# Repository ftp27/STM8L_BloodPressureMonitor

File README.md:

STM8L_BloodPressureMonitor
==========================

Bluetooth remote control for Blood Pressure Monitor on STM8L

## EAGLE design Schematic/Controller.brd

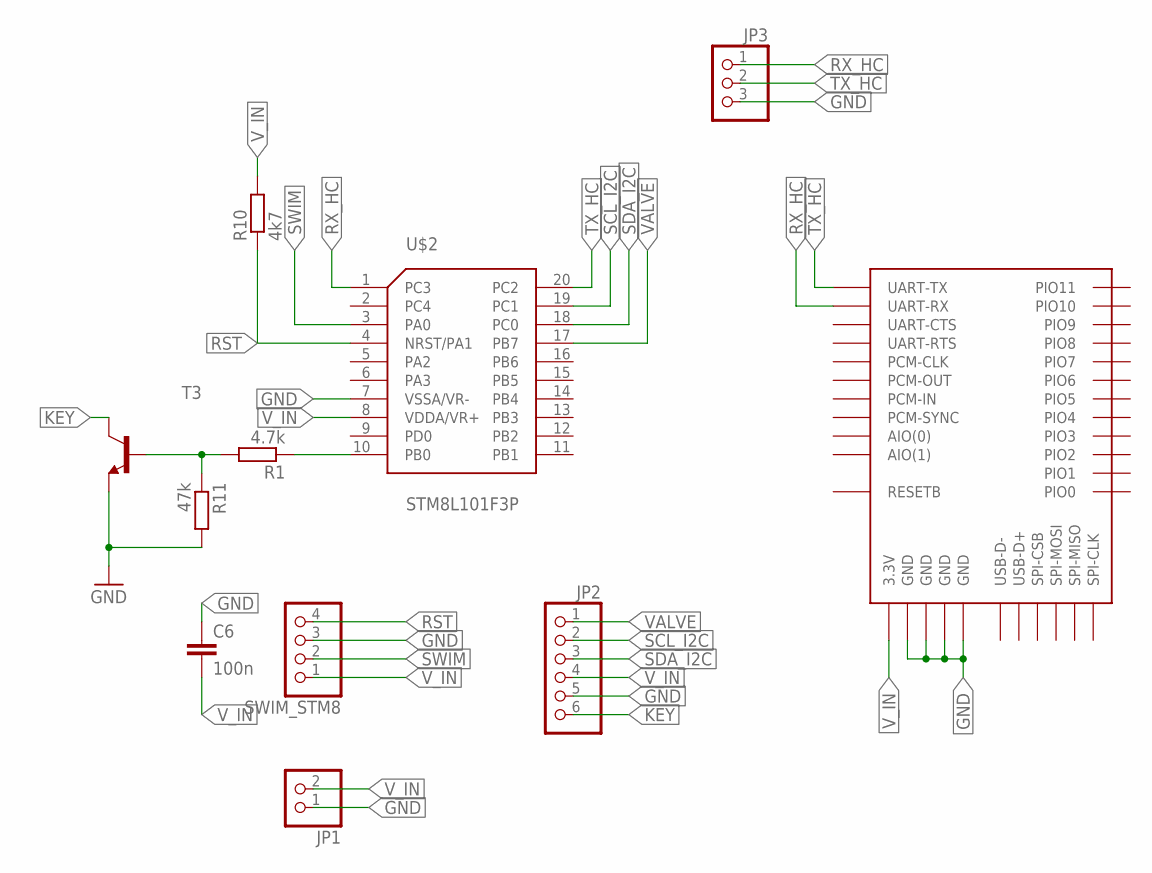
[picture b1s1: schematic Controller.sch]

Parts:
C6: 100n; C0805
JP1: PINHD-1X2; 1X02
JP2: PINHD-1X6; 1X06
JP3: PINHD-1X3; 1X03
R1: 4.7k; R0805
R10: 4k7; R0805
R11: 47k; R0805
SWIM_STM8: PINHD-1X4/90; 1X04/90
T3: BC846B-NPN-SOT23-BEC; SOT23-BEC
U$1: BTM400_6B
U$2: STM8L101F3P

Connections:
GND: C6.1, JP1.1, JP2.5, JP3.3, R11.2, SWIM_STM8.3, T3.E, U$1.GND@1 (GND), U$1.GND@2 (GND), U$1.GND@3 (GND), U$1.GND@4 (GND), U$2.7 (VSSA/VR-)
KEY: JP2.6, T3.C
unnamed: R1.1, U$2.10 (PB0)
unnamed: R1.2, R11.1, T3.B
RST: R10.1, SWIM_STM8.4, U$2.4 (NRST/PA1)
RX_HC: JP3.1, U$1.UART-RX, U$2.1 (PC3)
SCL_I2C: JP2.2, U$2.19 (PC1)
SDA_I2C: JP2.3, U$2.18 (PC0)
SWIM: SWIM_STM8.2, U$2.3 (PA0)
TX_HC: JP3.2, U$1.UART-TX, U$2.20 (PC2)
VALVE: JP2.1, U$2.17 (PB7)
V_IN: C6.2, JP1.2, JP2.4, R10.2, SWIM_STM8.1, U$1.3.3V, U$2.8 (VDDA/VR+)

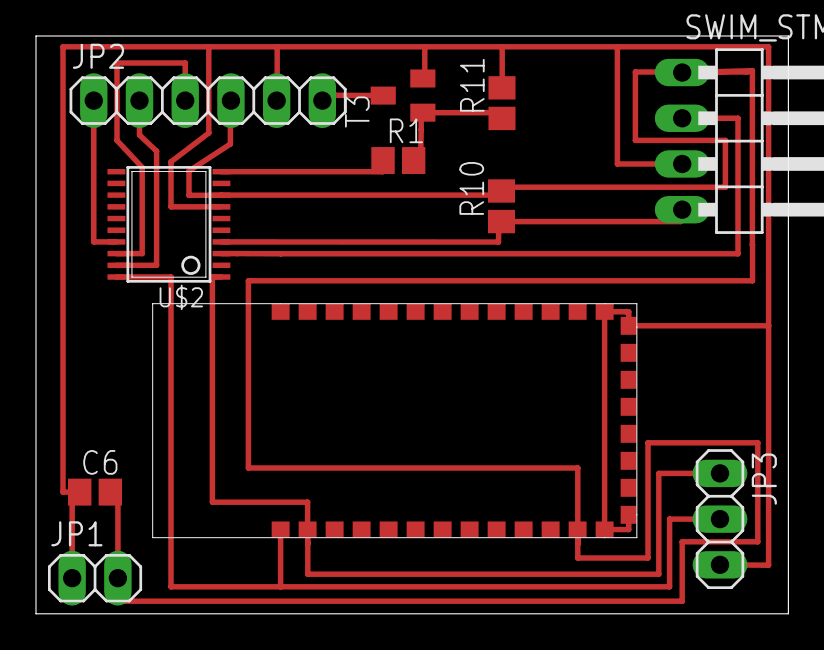
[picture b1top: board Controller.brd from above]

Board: 2 copper layers, 41.8 x 32.1 mm, 11 parts (0 on the bottom side), 12 nets.

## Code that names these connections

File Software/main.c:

// PC0 - I2C1_SDA
// PC1 - I2C1_SCL
// PC2 - USART1_RX
// PC3 - USART1_TX
#include "iostm8l152c6.h"

char getData(int address) {
  char result;
  
  char addressMSB = 0xA0 + ((address << 5) >> 12); 
  char addressLSB = ((address << 8) >> 8);
  
  I2C1_CR2_bit.START = 1; 
  while(!(I2C1_SR1_bit.SB));
    
  I2C1_DR = addressMSB+0; // For write
  while(!(I2C1_SR1_bit.ADDR));
  while(!(I2C1_SR1_bit.TXE));
  while(!(I2C1_SR3_bit.TRA));
  
  I2C1_DR = addressLSB;
  while(!(I2C1_SR1_bit.TXE));
  while(!(I2C1_SR1_bit.BTF));
    
  I2C1_CR2_bit.START = 1; // Repeated Start
  while(!(I2C1_SR1_bit.SB));
  
  I2C1_DR = addressMSB+1;
  while(!(I2C1_SR1_bit.ADDR));
  while(I2C1_SR3_bit.TRA);
 
  while(!(I2C1_SR1_bit.RXNE));  
  result = I2C1_DR;  
  
  while(!(I2C1_SR1_bit.BTF));
  
  I2C1_CR2_bit.STOP = 1;
  
  return result;
}

void delay (int time) {
  for (int i=0; i<time*1000; i++);
}

int main ( void )
{
  CLK_CKDIVR = 0x04;           // System clock source /16 == 1Mhz
  CLK_ICKCR_bit.HSION = 1;     // Clock ready
  CLK_PCKENR1_bit.PCKEN13 = 1; // I2C clock enable
  CLK_PCKENR1_bit.PCKEN15 = 1; // UART clock enable 
  
  // UART init
  USART1_CR1 = 0;
  USART1_CR3 = 0;
  USART1_CR4 = 0;
  USART1_CR5 = 0;
  
  USART1_BRR2 = 0x08;
  USART1_BRR1 = 0x06;
  
  USART1_CR2_bit.TEN = 1;
  USART1_CR2_bit.REN = 1;
  USART1_CR2_bit.RIEN = 1;
  
  // I2C init
  I2C1_FREQR = 0x01;            // Program the peripheral input clock in I2C_FREQR Register 
                                // in order to generate correct timings.
  I2C1_CCRL = 0x32;             // Configure the clock control registers
  I2C1_TRISER = 0x02;           // Configure the rise time register
  I2C1_CR1_bit.PE = 1;          // Program the I2C_CR1 register to enable the peripheral
  
  I2C1_OARL = 0xA0;
  I2C1_OARH_bit.ADDCONF = 1;
  
  for (unsigned int i=0x30; i<0x33; i++) {
     while(!(USART1_SR_bit.TXE));
     USART1_DR = getData(i);
  }
  
  asm("RIM");
  
  while (1);
}

#pragma vector=USART_R_OR_vector
__interrupt void USART_RXNE(void)
{ 
  char recive = USART1_DR;
}

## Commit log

2013-12-23 Firmware for get pressure from EEPROM
2013-12-24 Add schematic files
2013-12-26 Add firmware for stm8l101f3
2013-12-26 Deleted quartz resonator
2014-01-21 Fix firmware for UART transmit
2014-01-26 Removed Reset resistor, optimezed brd
